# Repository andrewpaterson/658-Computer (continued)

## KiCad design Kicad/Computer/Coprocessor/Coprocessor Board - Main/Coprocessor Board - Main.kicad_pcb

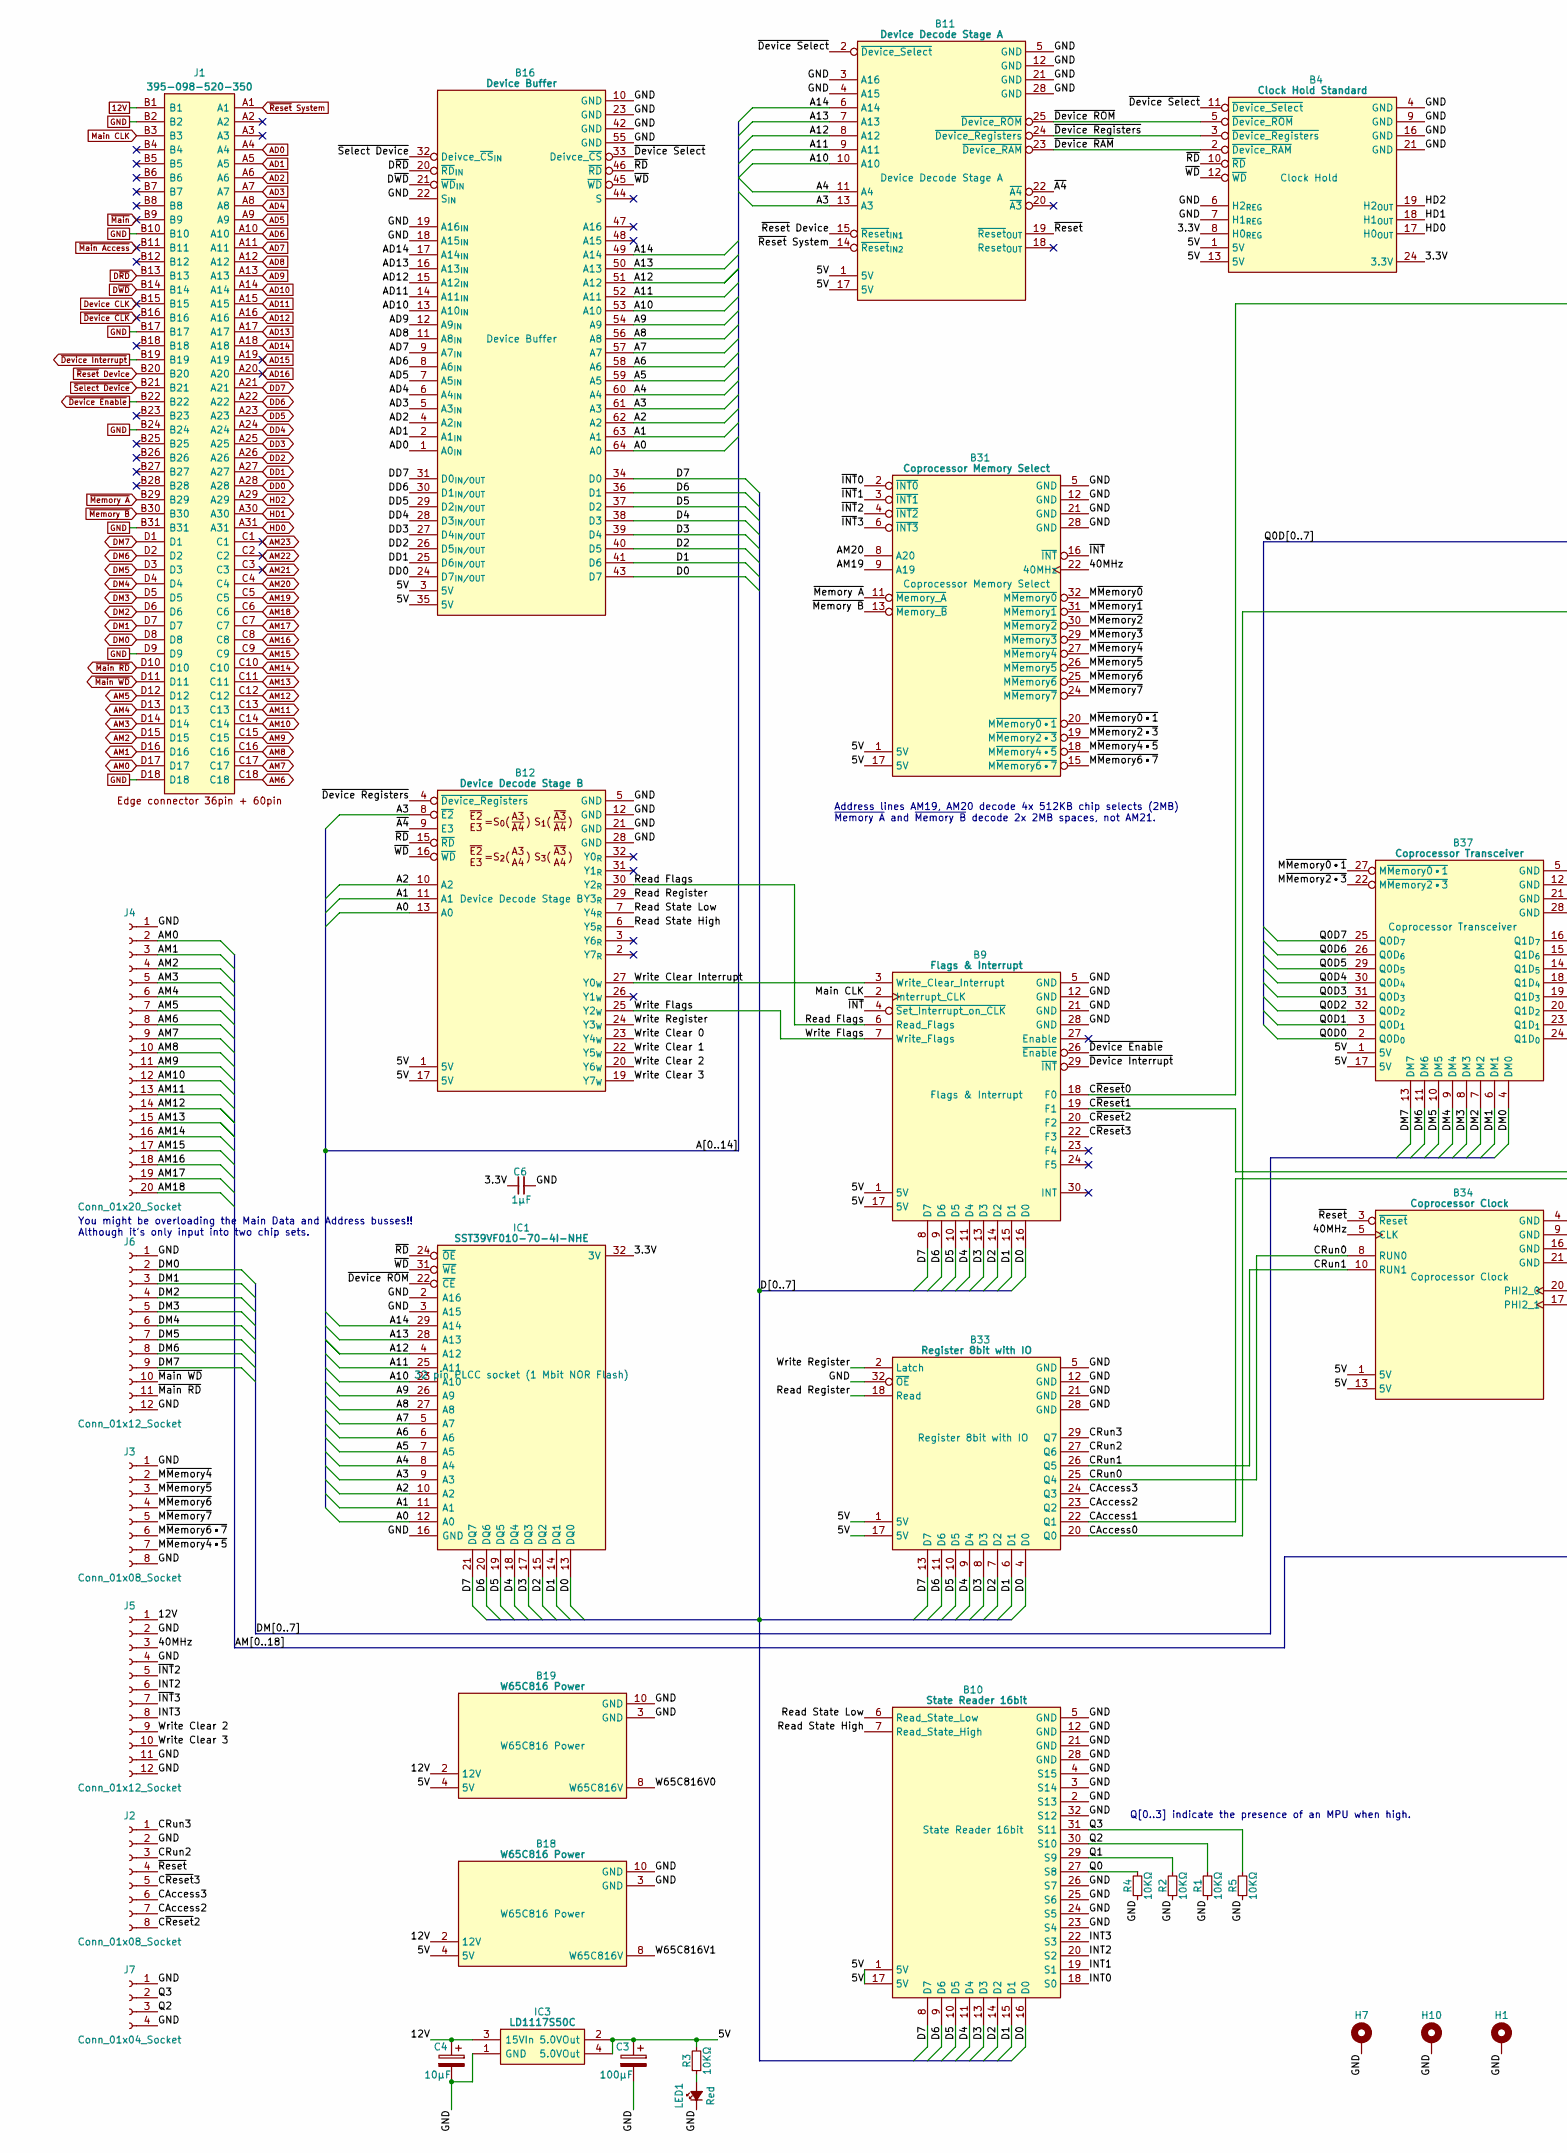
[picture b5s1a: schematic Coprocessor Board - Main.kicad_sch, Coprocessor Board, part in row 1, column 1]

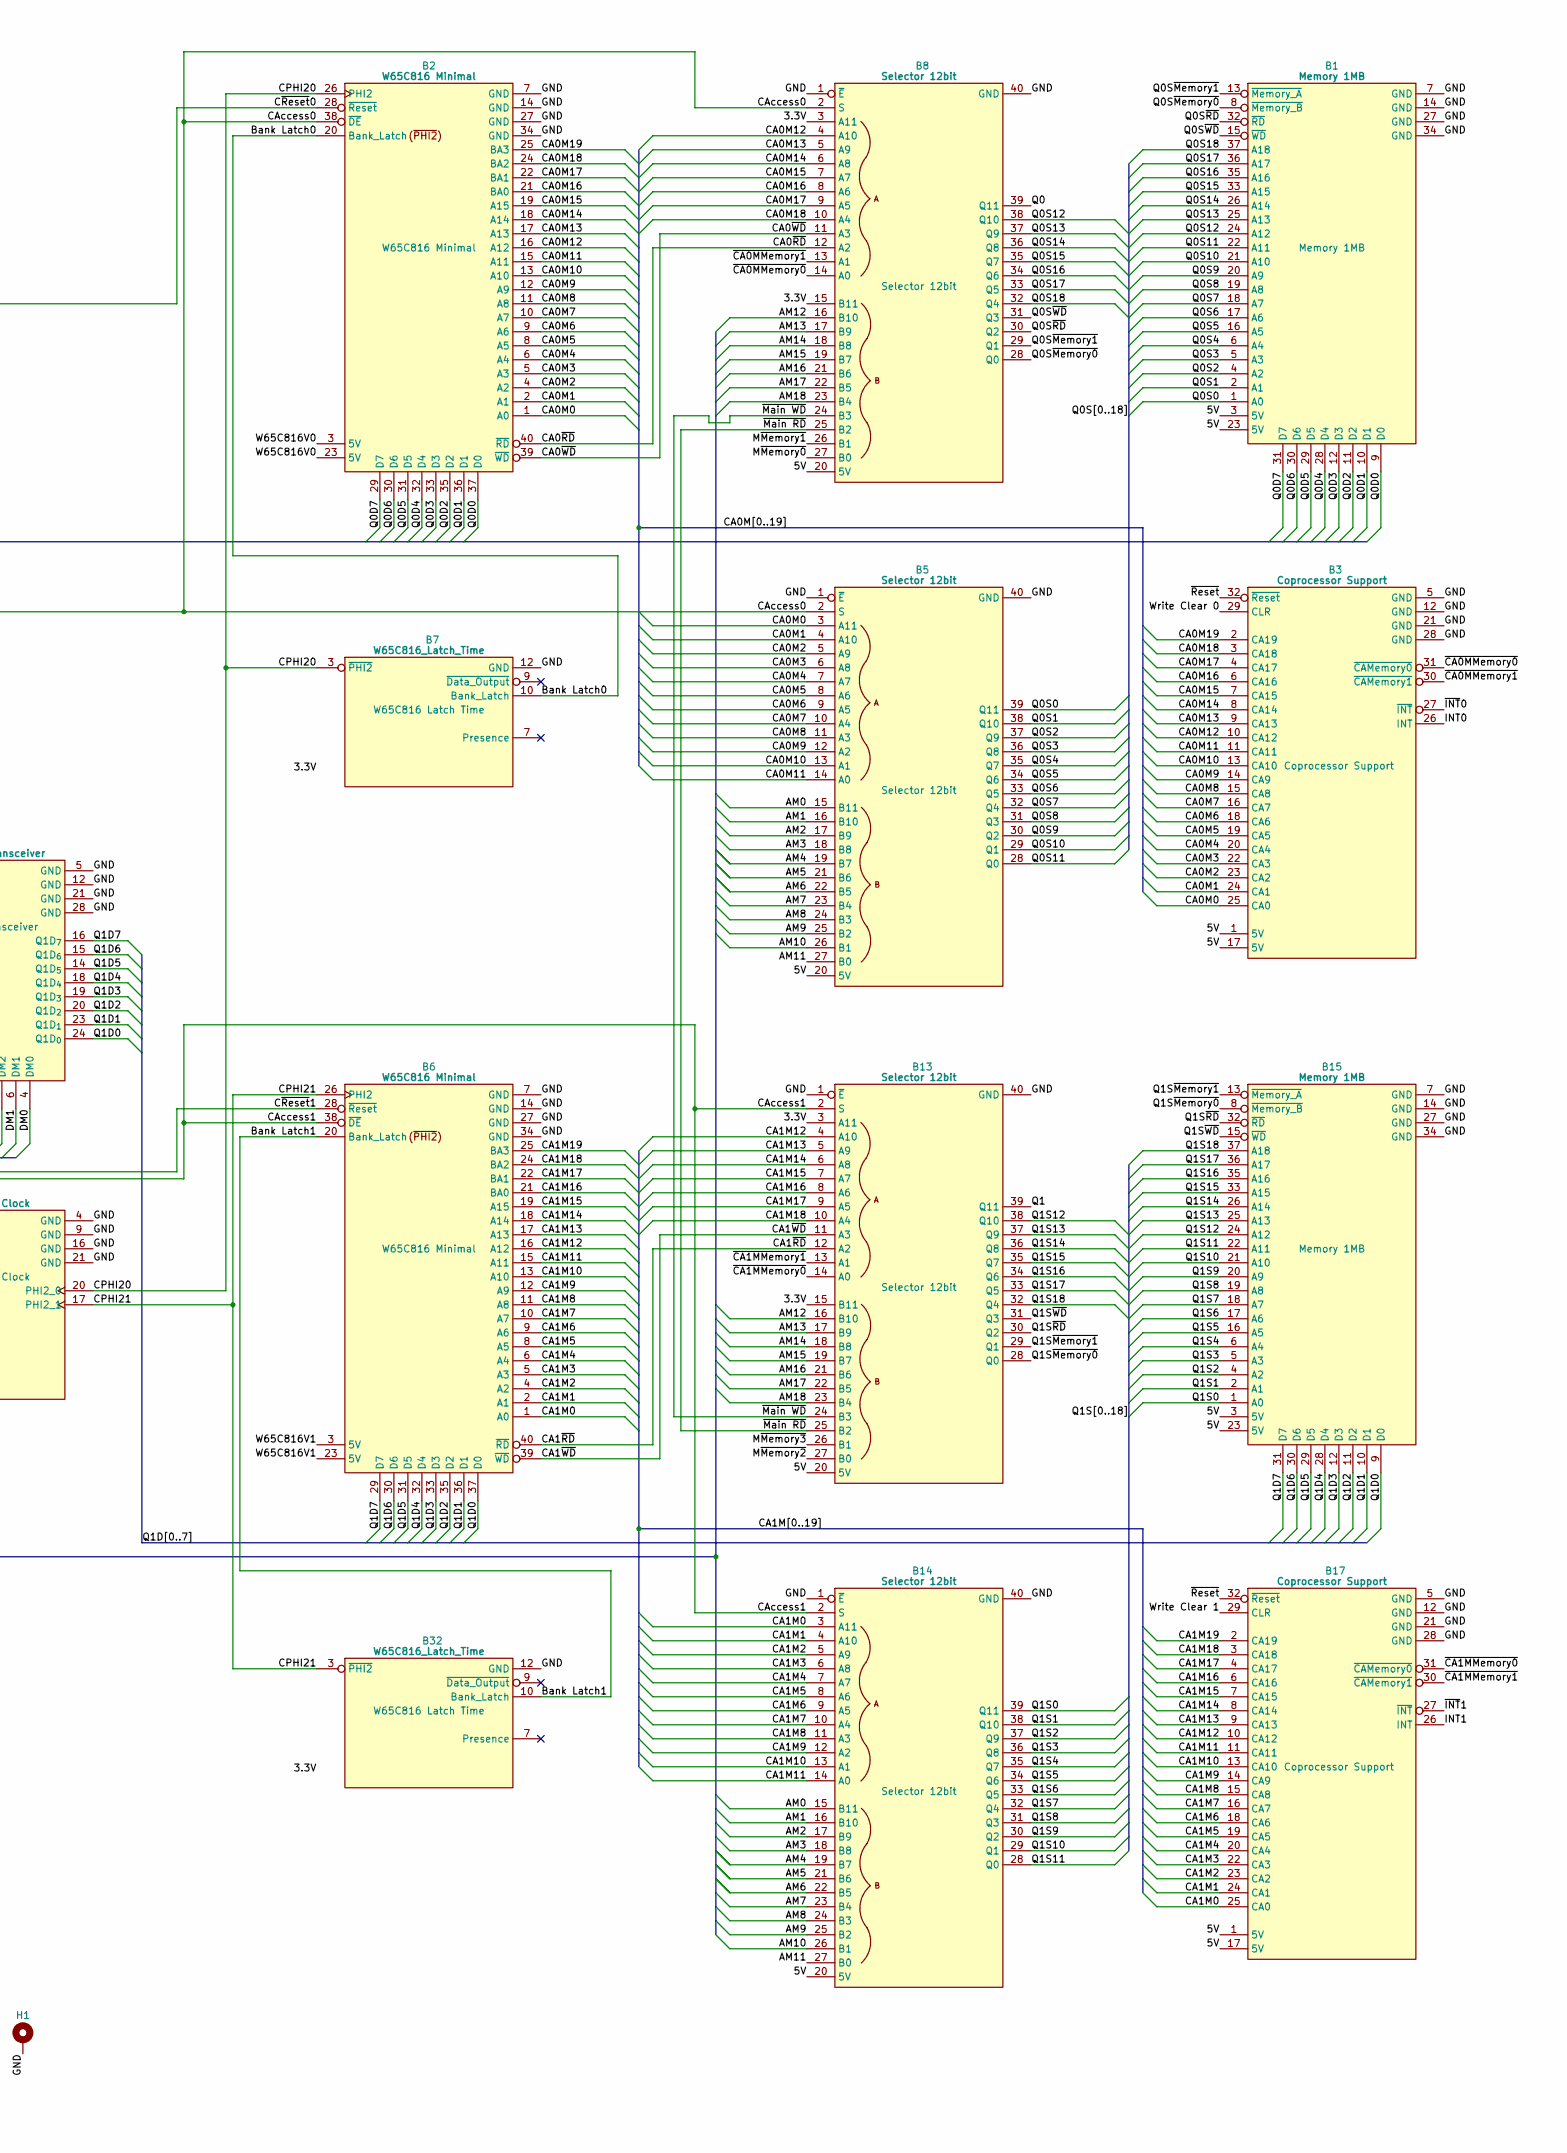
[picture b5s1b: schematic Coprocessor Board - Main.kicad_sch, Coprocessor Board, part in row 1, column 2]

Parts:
B1, B15: Memory 1MB; HCP65_Memory_1MB
B2, B6: W65C816 Minimal; HCP65_W65C816_Minimal
B3, B17: Coprocessor Support; HCP65_Coprocessor_Support
B4: Clock Hold Standard; HCP65_Clock_Hold_Standard
B5, B8, B13, B14: Selector 12bit; HCP65_Selector_12bit
B7, B32: W65C816_Latch_Time; HCP65_W65C816_Latch_Time
B9: Flags & Interrupt; HCP65_Flags_Interrupt
B10: State Reader 16bit; HCP65_State_Reader_16bit
B11: Device Decode Stage A; HCP65_Device_Decode_Stage_A
B12: Device Decode Stage B; HCP65_Device_Decode_Stage_B
B16: Device Buffer; HCP65_Device_Buffer
B18, B19: W65C816 Power; HCP65_W65C816_Power
B31: Coprocessor Memory Select; HCP65_Coprocessor_Memory_Select
B33: Register 8bit with IO; HCP65_Register_8bit_with_IO
B34: Coprocessor Clock; HCP65_Coprocessor_Clock
B37: Coprocessor Transceiver; HCP65_Coprocessor_Transceiver
C3: 100μF; CP_Radial_D4.0mm_P2.00mm
C4: 10μF; CP_Radial_D4.0mm_P2.00mm
C6: 1μF; C_0805
H1, H7, H10: MountingHole_Pad; HCP65_MountingHole_M3_
IC1: SST39VF010-70-4I-NHE; 5408803224008; Manufacturer_Part_Number SST39VF010-70-4I-NHE
IC3: LD1117S50C; LD1117S33C; Manufacturer_Part_Number LD1117S50C
J1: 395-098-520-350; 98pin Edge Connector; Manufacturer_Part_Number 395-098-520-350; Mouser Part Number 587-395-098-520-350
J2, J3: Conn_01x08_Socket; PinSocket_1x08_P2.54mm_Vertical
J4: Conn_01x20_Socket; PinSocket_1x20_P2.54mm_Vertical
J5, J6: Conn_01x12_Socket; PinSocket_1x12_P2.54mm_Vertical
J7: Conn_01x04_Socket; PinSocket_1x04_P2.54mm_Vertical
LED1: Red; LED_D5.0mm
R1, R2, R3, R4, R5: 10KΩ; R_0805

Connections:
12V: B18.2 (12V), B19.2 (12V), C4.1, IC3.3 (15VIn), J1.B1, J5.1
/3.3V: B4.8 (H0_{REG}), B4.24 (3.3V), B7.6 (3.3V), B8.3 (A11), B8.15 (B11), B13.3 (A11), B13.15 (B11), B32.6 (3.3V), C6.1, IC1.32 (3V)
/5V: B1.3 (5V), B1.23 (5V), B3.1 (5V), B3.17 (5V), B4.1 (5V), B4.13 (5V), B5.20 (5V), B8.20 (5V), B9.1 (5V), B9.17 (5V), B10.1 (5V), B10.17 (5V), B11.1 (5V), B11.17 (5V), B12.1 (5V), B12.17 (5V), B13.20 (5V), B14.20 (5V), B15.3 (5V), B15.23 (5V), B16.3 (5V), B16.35 (5V), B17.1 (5V), B17.17 (5V), B18.4 (5V), B19.4 (5V), B31.1 (5V), B31.17 (5V), B33.1 (5V), B33.17 (5V), B34.1 (5V), B34.13 (5V), B37.1 (5V), B37.17 (5V), C3.1, IC3.2 (5.0VOut), IC3.4 (5.0VOut), R3.2
/40MHz: B31.22 (40MHz), B34.5 (CLK), J5.3
/A0: B12.13 (A0), B16.64 (A0), IC1.12 (A0)
/A1: B12.11 (A1), B16.63 (A1), IC1.11 (A1)
/A2: B12.10 (A2), B16.62 (A2), IC1.10 (A2)
/A3: B11.13 (A3), B12.8 (~E2), B16.61 (A3), IC1.9 (A3)
/A4: B11.11 (A4), B16.60 (A4), IC1.8 (A4)
/A5: B16.59 (A5), IC1.7 (A5)
/A6: B16.58 (A6), IC1.6 (A6)
/A7: B16.57 (A7), IC1.5 (A7)
/A8: B16.56 (A8), IC1.27 (A8)
/A9: B16.54 (A9), IC1.26 (A9)
/A10: B11.10 (A10), B16.53 (A10), IC1.23 (A10)
/A11: B11.9 (A11), B16.52 (A11), IC1.25 (A11)
/A12: B11.8 (A12), B16.51 (A12), IC1.4 (A12)
/A13: B11.7 (A13), B16.50 (A13), IC1.28 (A13)
/A14: B11.6 (A14), B16.49 (A14), IC1.29 (A14)
/Bank Latch0: B2.20 (Bank_Latch), B7.10 (Bank_Latch)
/Bank Latch1: B6.20 (Bank_Latch), B32.10 (Bank_Latch)
/CA0M0: B2.1 (A0), B3.25 (CA0), B5.3 (A11)
/CA0M1: B2.2 (A1), B3.24 (CA1), B5.4 (A10)
/CA0M2: B2.4 (A2), B3.23 (CA2), B5.5 (A9)
/CA0M3: B2.5 (A3), B3.22 (CA3), B5.6 (A8)
/CA0M4: B2.6 (A4), B3.20 (CA4), B5.7 (A7)
/CA0M5: B2.8 (A5), B3.19 (CA5), B5.8 (A6)
/CA0M6: B2.9 (A6), B3.18 (CA6), B5.9 (A5)
/CA0M7: B2.10 (A7), B3.16 (CA7), B5.10 (A4)
/CA0M8: B2.11 (A8), B3.15 (CA8), B5.11 (A3)
/CA0M9: B2.12 (A9), B3.14 (CA9), B5.12 (A2)
/CA0M10: B2.13 (A10), B3.13 (CA10), B5.13 (A1)
/CA0M11: B2.15 (A11), B3.11 (CA11), B5.14 (A0)
/CA0M12: B2.16 (A12), B3.10 (CA12), B8.4 (A10)
/CA0M13: B2.17 (A13), B3.9 (CA13), B8.5 (A9)
/CA0M14: B2.18 (A14), B3.8 (CA14), B8.6 (A8)
/CA0M15: B2.19 (A15), B3.7 (CA15), B8.7 (A7)
/CA0M16: B2.21 (BA0), B3.6 (CA16), B8.8 (A6)
/CA0M17: B2.22 (BA1), B3.4 (CA17), B8.9 (A5)
/CA0M18: B2.24 (BA2), B3.3 (CA18), B8.10 (A4)
/CA0M19: B2.25 (BA3), B3.2 (CA19)
/CA0~RD: B2.40 (~RD), B8.12 (A2)
/CA0~WD: B2.39 (~WD), B8.11 (A3)
/CA1M0: B6.1 (A0), B14.3 (A11), B17.25 (CA0)
/CA1M1: B6.2 (A1), B14.4 (A10), B17.24 (CA1)
/CA1M2: B6.4 (A2), B14.5 (A9), B17.23 (CA2)
/CA1M3: B6.5 (A3), B14.6 (A8), B17.22 (CA3)
/CA1M4: B6.6 (A4), B14.7 (A7), B17.20 (CA4)
/CA1M5: B6.8 (A5), B14.8 (A6), B17.19 (CA5)
/CA1M6: B6.9 (A6), B14.9 (A5), B17.18 (CA6)
/CA1M7: B6.10 (A7), B14.10 (A4), B17.16 (CA7)
/CA1M8: B6.11 (A8), B14.11 (A3), B17.15 (CA8)
/CA1M9: B6.12 (A9), B14.12 (A2), B17.14 (CA9)
/CA1M10: B6.13 (A10), B14.13 (A1), B17.13 (CA10)
/CA1M11: B6.15 (A11), B14.14 (A0), B17.11 (CA11)
/CA1M12: B6.16 (A12), B13.4 (A10), B17.10 (CA12)
/CA1M13: B6.17 (A13), B13.5 (A9), B17.9 (CA13)
/CA1M14: B6.18 (A14), B13.6 (A8), B17.8 (CA14)
/CA1M15: B6.19 (A15), B13.7 (A7), B17.7 (CA15)
/CA1M16: B6.21 (BA0), B13.8 (A6), B17.6 (CA16)
/CA1M17: B6.22 (BA1), B13.9 (A5), B17.4 (CA17)
/CA1M18: B6.24 (BA2), B13.10 (A4), B17.3 (CA18)
/CA1M19: B6.25 (BA3), B17.2 (CA19)
/CA1~RD: B6.40 (~RD), B13.12 (A2)
/CA1~WD: B6.39 (~WD), B13.11 (A3)
/CAccess0: B2.38 (~DE), B5.2 (S), B8.2 (S), B33.20 (Q0)
/CAccess1: B6.38 (~DE), B13.2 (S), B14.2 (S), B33.22 (Q1)
/CAccess2: B33.23 (Q2), J2.7
/CAccess3: B33.24 (Q3), J2.6
/CPHI20: B2.26 (PHI2), B7.3 (~PHI2), B34.20 (PHI2_0)
/CPHI21: B6.26 (PHI2), B32.3 (~PHI2), B34.17 (PHI2_1)
/CRun0: B33.25 (Q4), B34.8 (RUN0)
/CRun1: B33.26 (Q5), B34.10 (RUN1)
/CRun2: B33.27 (Q6), J2.3
/CRun3: B33.29 (Q7), J2.1
/C~Reset0: B2.28 (~Reset), B9.18 (F0)
/C~Reset1: B6.28 (~Reset), B9.19 (F1)
/C~Reset2: B9.20 (F2), J2.8
/C~Reset3: B9.22 (F3), J2.5
/D0: B9.16 (D0), B10.16 (D0), B16.43 (D7), B33.4 (D0), IC1.13 (DQ0)
/D1: B9.15 (D1), B10.15 (D1), B16.41 (D6), B33.6 (D1), IC1.14 (DQ1)
/D2: B9.14 (D2), B10.14 (D2), B16.40 (D5), B33.7 (D2), IC1.15 (DQ2)
/D3: B9.13 (D3), B10.13 (D3), B16.39 (D4), B33.8 (D3), IC1.17 (DQ3)
/D4: B9.11 (D4), B10.11 (D4), B16.38 (D3), B33.9 (D4), IC1.18 (DQ4)
/D5: B9.10 (D5), B10.10 (D5), B16.37 (D2), B33.10 (D5), IC1.19 (DQ5)
/D6: B9.9 (D6), B10.9 (D6), B16.36 (D1), B33.11 (D6), IC1.20 (DQ6)
/D7: B9.8 (D7), B10.8 (D7), B16.34 (D0), B33.13 (D7), IC1.21 (DQ7)
/INT0: B3.26 (INT), B10.18 (S0)
/INT1: B10.19 (S1), B17.26 (INT)
/INT2: B10.20 (S2), J5.6
/INT3: B10.22 (S3), J5.8
/M~Memory0: B8.27 (B0), B31.32 (M~Memory0)
/M~Memory0•1: B31.20 (M~Memory0•1), B37.27 (M~Memory0•1)
/M~Memory1: B8.26 (B1), B31.31 (M~Memory1)
/M~Memory2: B13.27 (B0), B31.30 (M~Memory2)
/M~Memory2•3: B31.19 (M~Memory2•3), B37.22 (M~Memory2•3)
/M~Memory3: B13.26 (B1), B31.29 (M~Memory3)
/M~Memory4: B31.27 (M~Memory4), J3.2
/M~Memory4•5: B31.18 (M~Memory4•5), J3.7
/M~Memory5: B31.26 (M~Memory5), J3.3
/M~Memory6: B31.25 (M~Memory6), J3.4
/M~Memory6•7: B31.15 (M~Memory6•7), J3.6
/M~Memory7: B31.24 (M~Memory7), J3.5
/Q0: B8.39 (Q11), B10.27 (S8), R4.2
/Q0D0: B1.9 (D0), B2.37 (D0), B37.2 (Q0D_{0})
/Q0D1: B1.10 (D1), B2.36 (D1), B37.3 (Q0D_{1})
/Q0D2: B1.11 (D2), B2.35 (D2), B37.32 (Q0D_{2})
/Q0D3: B1.12 (D3), B2.33 (D3), B37.31 (Q0D_{3})
/Q0D4: B1.28 (D4), B2.32 (D4), B37.30 (Q0D_{4})
/Q0D5: B1.29 (D5), B2.31 (D5), B37.29 (Q0D_{5})
/Q0D6: B1.30 (D6), B2.30 (D6), B37.26 (Q0D_{6})
/Q0D7: B1.31 (D7), B2.29 (D7), B37.25 (Q0D_{7})
/Q0S0: B1.1 (A0), B5.39 (Q11)
/Q0S1: B1.2 (A1), B5.38 (Q10)
/Q0S2: B1.4 (A2), B5.37 (Q9)
/Q0S3: B1.5 (A3), B5.36 (Q8)
/Q0S4: B1.6 (A4), B5.35 (Q7)
/Q0S5: B1.16 (A5), B5.34 (Q6)
/Q0S6: B1.17 (A6), B5.33 (Q5)
/Q0S7: B1.18 (A7), B5.32 (Q4)
/Q0S8: B1.19 (A8), B5.31 (Q3)
/Q0S9: B1.20 (A9), B5.30 (Q2)
/Q0S10: B1.21 (A10), B5.29 (Q1)
/Q0S11: B1.22 (A11), B5.28 (Q0)
/Q0S12: B1.24 (A12), B8.38 (Q10)
/Q0S13: B1.25 (A13), B8.37 (Q9)
/Q0S14: B1.26 (A14), B8.36 (Q8)
/Q0S15: B1.33 (A15), B8.35 (Q7)
/Q0S16: B1.35 (A16), B8.34 (Q6)
/Q0S17: B1.36 (A17), B8.33 (Q5)
/Q0S18: B1.37 (A18), B8.32 (Q4)
/Q0S~Memory0: B1.8 (~Memory_B), B8.28 (Q0)
/Q0S~Memory1: B1.13 (~Memory_A), B8.29 (Q1)
/Q0S~RD: B1.32 (~RD), B8.30 (Q2)
/Q0S~WD: B1.15 (~WD), B8.31 (Q3)
/Q1: B10.29 (S9), B13.39 (Q11), R2.2
/Q1D0: B6.37 (D0), B15.9 (D0), B37.24 (Q1D_{0})
/Q1D1: B6.36 (D1), B15.10 (D1), B37.23 (Q1D_{1})
/Q1D2: B6.35 (D2), B15.11 (D2), B37.20 (Q1D_{2})
/Q1D3: B6.33 (D3), B15.12 (D3), B37.19 (Q1D_{3})
/Q1D4: B6.32 (D4), B15.28 (D4), B37.18 (Q1D_{4})
/Q1D5: B6.31 (D5), B15.29 (D5), B37.14 (Q1D_{5})
/Q1D6: B6.30 (D6), B15.30 (D6), B37.15 (Q1D_{6})
/Q1D7: B6.29 (D7), B15.31 (D7), B37.16 (Q1D_{7})
/Q1S0: B14.39 (Q11), B15.1 (A0)
/Q1S1: B14.38 (Q10), B15.2 (A1)
/Q1S2: B14.37 (Q9), B15.4 (A2)
/Q1S3: B14.36 (Q8), B15.5 (A3)
/Q1S4: B14.35 (Q7), B15.6 (A4)
/Q1S5: B14.34 (Q6), B15.16 (A5)
/Q1S6: B14.33 (Q5), B15.17 (A6)
/Q1S7: B14.32 (Q4), B15.18 (A7)
/Q1S8: B14.31 (Q3), B15.19 (A8)
/Q1S9: B14.30 (Q2), B15.20 (A9)
/Q1S10: B14.29 (Q1), B15.21 (A10)
/Q1S11: B14.28 (Q0), B15.22 (A11)
/Q1S12: B13.38 (Q10), B15.24 (A12)
/Q1S13: B13.37 (Q9), B15.25 (A13)
/Q1S14: B13.36 (Q8), B15.26 (A14)
/Q1S15: B13.35 (Q7), B15.33 (A15)
/Q1S16: B13.34 (Q6), B15.35 (A16)
/Q1S17: B13.33 (Q5), B15.36 (A17)
/Q1S18: B13.32 (Q4), B15.37 (A18)
/Q1S~Memory0: B13.28 (Q0), B15.8 (~Memory_B)
/Q1S~Memory1: B13.29 (Q1), B15.13 (~Memory_A)
/Q1S~RD: B13.30 (Q2), B15.32 (~RD)
/Q1S~WD: B13.31 (Q3), B15.15 (~WD)
/Q2: B10.30 (S10), J7.3, R1.2
/Q3: B10.31 (S11), J7.2, R5.2
/Read Flags: B9.6 (Read_Flags), B12.30 (Y2_{R})
/Read Register: B12.29 (Y3_{R}), B33.18 (Read)
/Read State High: B10.7 (Read_State_High), B12.6 (Y5_{R})
/Read State Low: B10.6 (Read_State_Low), B12.7 (Y4_{R})
/W65C816V0: B2.3 (5V), B2.23 (5V), B19.8 (W65C816V)
/W65C816V1: B6.3 (5V), B6.23 (5V), B18.8 (W65C816V)
/Write Clear 0: B3.29 (CLR), B12.23 (Y4_{W})
/Write Clear 1: B12.22 (Y5_{W}), B17.29 (CLR)
/Write Clear 2: B12.20 (Y6_{W}), J5.9
/Write Clear 3: B12.19 (Y7_{W}), J5.10
/Write Clear Interrupt: B9.3 (Write_Clear_Interrupt), B12.27 (Y0_{W})
/Write Flags: B9.7 (Write_Flags), B12.25 (Y2_{W})
/Write Register: B12.24 (Y3_{W}), B33.2 (Latch)
/~A4: B11.22 (~A4), B12.9 (E3)
/~CA0MMemory0: B3.31 (~CAMemory0), B8.14 (A0)
/~CA0MMemory1: B3.30 (~CAMemory1), B8.13 (A1)
/~CA1MMemory0: B13.14 (A0), B17.31 (~CAMemory0)
/~CA1MMemory1: B13.13 (A1), B17.30 (~CAMemory1)
/~Device RAM: B4.2 (~Device_RAM), B11.23 (~Device_RAM)
/~Device ROM: B4.5 (~Device_ROM), B11.25 (~Device_ROM), IC1.22 (~CE)
/~Device Registers: B4.3 (~Device_Registers), B11.24 (~Device_Registers), B12.4 (~Device_Registers)
/~Device Select: B4.11 (~Device_Select), B11.2 (~Device_Select), B16.33 (Deivce_~CS)
/~INT: B9.4 (~Set_Interrupt_on_CLK), B31.16 (~INT)
/~INT0: B3.27 (~INT), B31.2 (~INT0)
/~INT1: B17.27 (~INT), B31.3 (~INT1)
/~INT2: B31.4 (~INT2), J5.5
/~INT3: B31.6 (~INT3), J5.7
/~RD: B4.10 (~RD), B12.15 (~RD), B16.46 (~RD), IC1.24 (~OE)
/~Reset: B3.32 (~Reset), B11.19 (~Reset_{OUT}), B17.32 (~Reset), B34.3 (~Reset), J2.4
/~WD: B4.12 (~WD), B12.16 (~WD), B16.45 (~WD), IC1.31 (~WE)
AD0: B16.1 (A0_{IN}), J1.A4
AD1: B16.2 (A1_{IN}), J1.A5
AD2: B16.4 (A2_{IN}), J1.A6
AD3: B16.5 (A3_{IN}), J1.A7
AD4: B16.6 (A4_{IN}), J1.A8
AD5: B16.7 (A5_{IN}), J1.A9
AD6: B16.8 (A6_{IN}), J1.A10
AD7: B16.9 (A7_{IN}), J1.A11
AD8: B16.11 (A8_{IN}), J1.A12
AD9: B16.12 (A9_{IN}), J1.A13
AD10: B16.13 (A10_{IN}), J1.A14
AD11: B16.14 (A11_{IN}), J1.A15
AD12: B16.15 (A12_{IN}), J1.A16
AD13: B16.16 (A13_{IN}), J1.A17
AD14: B16.17 (A14_{IN}), J1.A18
AD15: J1.A19
AD16: J1.A20
AM0: B5.15 (B11), B14.15 (B11), J1.D17, J4.2
AM1: B5.16 (B10), B14.16 (B10), J1.D16, J4.3
AM2: B5.17 (B9), B14.17 (B9), J1.D15, J4.4
AM3: B5.18 (B8), B14.18 (B8), J1.D14, J4.5
AM4: B5.19 (B7), B14.19 (B7), J1.D13, J4.6
AM5: B5.21 (B6), B14.21 (B6), J1.D12, J4.7
AM6: B5.22 (B5), B14.22 (B5), J1.C18, J4.8
AM7: B5.23 (B4), B14.23 (B4), J1.C17, J4.9
AM8: B5.24 (B3), B14.24 (B3), J1.C16, J4.10
AM9: B5.25 (B2), B14.25 (B2), J1.C15, J4.11
AM10: B5.26 (B1), B14.26 (B1), J1.C14, J4.12
AM11: B5.27 (B0), B14.27 (B0), J1.C13, J4.13
AM12: B8.16 (B10), B13.16 (B10), J1.C12, J4.14
AM13: B8.17 (B9), B13.17 (B9), J1.C11, J4.15
AM14: B8.18 (B8), B13.18 (B8), J1.C10, J4.16
AM15: B8.19 (B7), B13.19 (B7), J1.C9, J4.17
AM16: B8.21 (B6), B13.21 (B6), J1.C8, J4.18
AM17: B8.22 (B5), B13.22 (B5), J1.C7, J4.19
AM18: B8.23 (B4), B13.23 (B4), J1.C6, J4.20
AM19: B31.9 (A19), J1.C5
AM20: B31.8 (A20), J1.C4
AM21: J1.C3
AM22: J1.C2
AM23: J1.C1
DD0: B16.24 (D7_{IN/OUT}), J1.A28
DD1: B16.25 (D6_{IN/OUT}), J1.A27
DD2: B16.26 (D5_{IN/OUT}), J1.A26
DD3: B16.27 (D4_{IN/OUT}), J1.A25
DD4: B16.28 (D3_{IN/OUT}), J1.A24
DD5: B16.29 (D2_{IN/OUT}), J1.A23
DD6: B16.30 (D1_{IN/OUT}), J1.A22
DD7: B16.31 (D0_{IN/OUT}), J1.A21
DM0: B37.4 (DM0), J1.D8, J6.2
DM1: B37.6 (DM1), J1.D7, J6.3
DM2: B37.7 (DM2), J1.D6, J6.4
DM3: B37.8 (DM3), J1.D5, J6.5
DM4: B37.9 (DM4), J1.D4, J6.6
DM5: B37.10 (DM5), J1.D3, J6.7
DM6: B37.11 (DM6), J1.D2, J6.8
DM7: B37.13 (DM7), J1.D1, J6.9
Device CLK: J1.B15
D~RD: B16.20 (~RD_{IN}), J1.B13
D~WD: B16.21 (~WD_{IN}), J1.B14
GND: B1.7 (GND), B1.14 (GND), B1.27 (GND), B1.34 (GND), B2.7 (GND), B2.14 (GND), B2.27 (GND), B2.34 (GND), B3.5 (GND), B3.12 (GND), B3.21 (GND), B3.28 (GND), B4.4 (GND), B4.6 (H2_{REG}), B4.7 (H1_{REG}), B4.9 (GND), B4.16 (GND), B4.21 (GND), B5.1 (~E), B5.40 (GND), B6.7 (GND), B6.14 (GND), B6.27 (GND), B6.34 (GND), B7.12 (GND), B8.1 (~E), B8.40 (GND), B9.5 (GND), B9.12 (GND), B9.21 (GND), B9.28 (GND), B10.2 (S13), B10.3 (S14), B10.4 (S15), B10.5 (GND), B10.12 (GND), B10.21 (GND), B10.23 (S4), B10.24 (S5), B10.25 (S6), B10.26 (S7), B10.28 (GND), B10.32 (S12), B11.3 (A16), B11.4 (A15), B11.5 (GND), B11.12 (GND), B11.21 (GND), B11.28 (GND), B12.5 (GND), B12.12 (GND), B12.21 (GND), B12.28 (GND), B13.1 (~E), B13.40 (GND), B14.1 (~E), B14.40 (GND), B15.7 (GND), B15.14 (GND), B15.27 (GND), B15.34 (GND), B16.10 (GND), B16.18 (A15_{IN}), B16.19 (A16_{IN}), B16.22 (S_{IN}), B16.23 (GND), B16.42 (GND), B16.55 (GND), B17.5 (GND), B17.12 (GND), B17.21 (GND), B17.28 (GND), B18.3 (GND), B18.10 (GND), B19.3 (GND), B19.10 (GND), B31.5 (GND), B31.12 (GND), B31.21 (GND), B31.28 (GND), B32.12 (GND), B33.5 (GND), B33.12 (GND), B33.21 (GND), B33.28 (GND), B33.32 (~OE), B34.4 (GND), B34.9 (GND), B34.16 (GND), B34.21 (GND), B37.5 (GND), B37.12 (GND), B37.21 (GND), B37.28 (GND), C3.2, C4.2, C6.2, H1.1 (GND), H7.1 (GND), H10.1 (GND), IC1.2 (A16), IC1.3 (A15), IC1.16 (GND), IC3.1 (GND), J1.B2, J1.B10, J1.B17, J1.B24, J1.B31, J1.D9, J1.D18, J2.2, J3.1, J3.8, J4.1, J5.2, J5.4, J5.11, J5.12, J6.1, J6.12, J7.1, J7.4, LED1.1 (K), R1.1, R2.1, R4.1, R5.1
HD0: B4.17 (H0_{OUT}), J1.A31
HD1: B4.18 (H1_{OUT}), J1.A30
HD2: B4.19 (H2_{OUT}), J1.A29
Main CLK: B9.2 (Interrupt_CLK), J1.B3
unnamed: LED1.2 (A), R3.1
~Device CLK: J1.B16
~Device Enable: B9.26 (~Enable), J1.B22
~Device Interrupt: B9.29 (~INT), J1.B19
~Main Access: J1.B11
~Main RD: B8.25 (B2), B13.25 (B2), J1.D10, J6.11
~Main WD: B8.24 (B3), B13.24 (B3), J1.D11, J6.10
~Main: J1.B9
~Memory A: B31.11 (~Memory_A), J1.B29
~Memory B: B31.13 (~Memory_B), J1.B30
~Reset Device: B11.15 (~Reset_{IN1}), J1.B20
~Reset System: B11.14 (~Reset_{IN2}), J1.A1
~Select Device: B16.32 (Deivce_~CS_{IN}), J1.B21

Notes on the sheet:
Q[0..3] indicate the presence of an MPU when high.
You might be overloading the Main Data and Address busses!! Although it's only input into two chip sets.
Address lines AM19, AM20 decode 4x 512KB chip selects (2MB) ~{Memory A} and ~{Memory B} decode 2x 2MB spaces, not AM21.

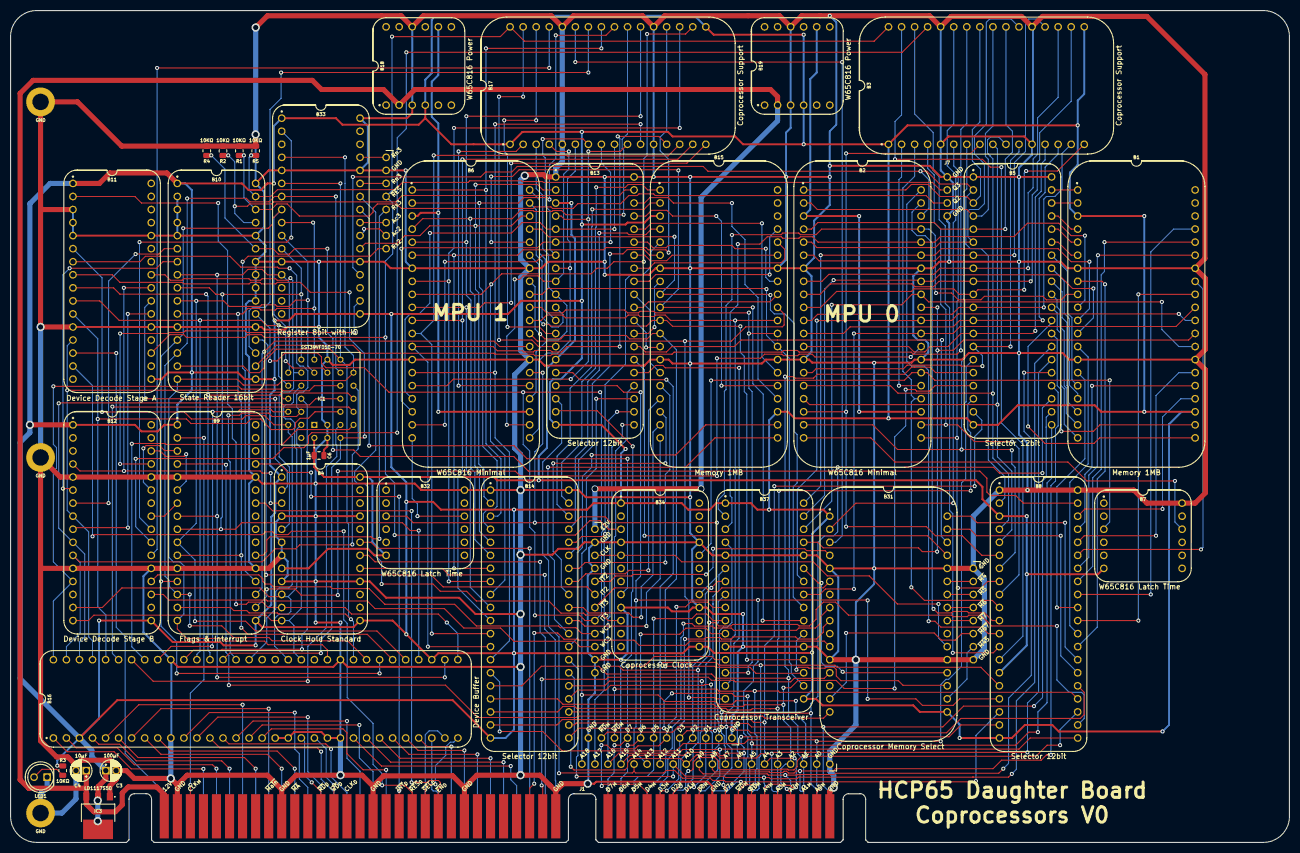
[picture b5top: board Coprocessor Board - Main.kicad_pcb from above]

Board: 2 copper layers, 248.9 x 161.9 mm, 45 parts (0 on the bottom side), 268 nets.

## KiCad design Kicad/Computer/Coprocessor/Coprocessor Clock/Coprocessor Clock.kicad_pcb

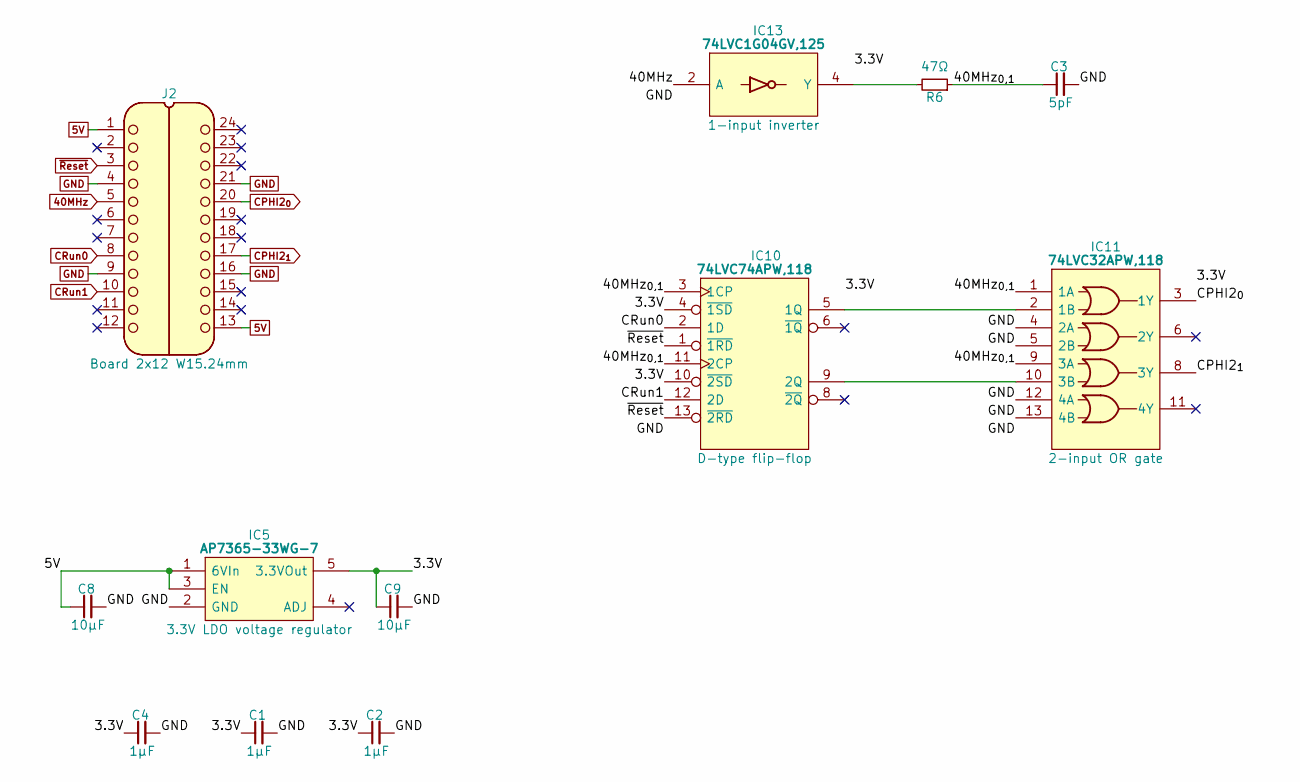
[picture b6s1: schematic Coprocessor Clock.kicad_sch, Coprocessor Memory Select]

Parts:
C1, C2, C4: 1μF; C_0805
C3: 5pF; C_0805
C8, C9: 10µF; C_0805
IC5: AP7365-33WG-7; SOT95P285X130-5N; Manufacturer_Part_Number AP7365-33WG-7; Mouser Part Number 621-AP7365-33WG-7
IC10: 74LVC74APW,118; SOP65P640X110-14N; Mouser Part Number 771-74LVC74APW-T
IC11: 74LVC32APW,118; SOP65P640X110-14N; Manufacturer_Part_Number 74LVC32APW,118; Mouser Part Number 771-74LVC32APW-T
IC13: 74LVC1G04GV,125; SOT95P275X110-5N; Manufacturer_Part_Number 74LVC1G04GV,125; Mouser Part Number 771-74LVC1G04GV
J2: Board 2x12 W15.24mm; DIP-24_Board_W15.24mm
R6: 47Ω; R_0805

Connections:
5V: C8.1, IC5.1 (6VIn), IC5.3 (EN), J2.1, J2.13
40MHz: IC13.2 (A), J2.5
/3.3V: C1.1, C2.1, C4.1, C9.1, IC5.5 (3.3VOut), IC10.4 (~1SD), IC10.10 (~2SD), IC10.14 (3V), IC11.14 (3V), IC13.5 (3V)
/40MHz_{0,1}: C3.1, IC10.3 (1CP), IC10.11 (2CP), IC11.1 (1A), IC11.9 (3A), R6.1
CPHI2_{0}: IC11.3 (1Y), J2.20
CPHI2_{1}: IC11.8 (3Y), J2.17
CRun0: IC10.2 (1D), J2.8
CRun1: IC10.12 (2D), J2.10
GND: C1.2, C2.2, C3.2, C4.2, C8.2, C9.2, IC5.2 (GND), IC10.7 (GND), IC11.4 (2A), IC11.5 (2B), IC11.7 (GND), IC11.12 (4A), IC11.13 (4B), IC13.3 (GND), J2.4, J2.9, J2.16, J2.21
unnamed: IC10.5 (1Q), IC11.2 (1B)
unnamed: IC10.9 (2Q), IC11.10 (3B)
unnamed: IC13.4 (Y), R6.2
~Reset: IC10.1 (~1RD), IC10.13 (~2RD), J2.3

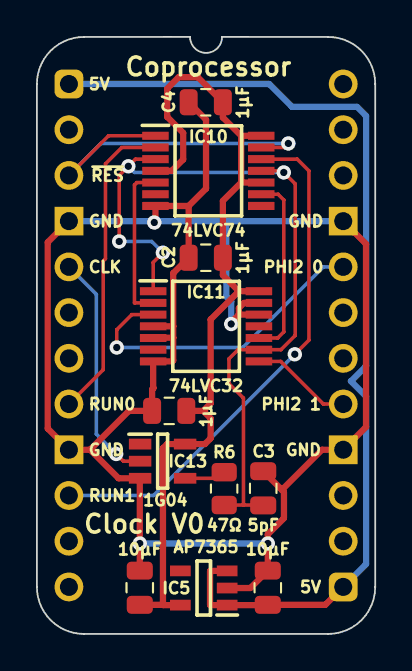
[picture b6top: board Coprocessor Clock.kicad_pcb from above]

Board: 2 copper layers, 18.8 x 33.2 mm, 12 parts (0 on the bottom side), 13 nets.
